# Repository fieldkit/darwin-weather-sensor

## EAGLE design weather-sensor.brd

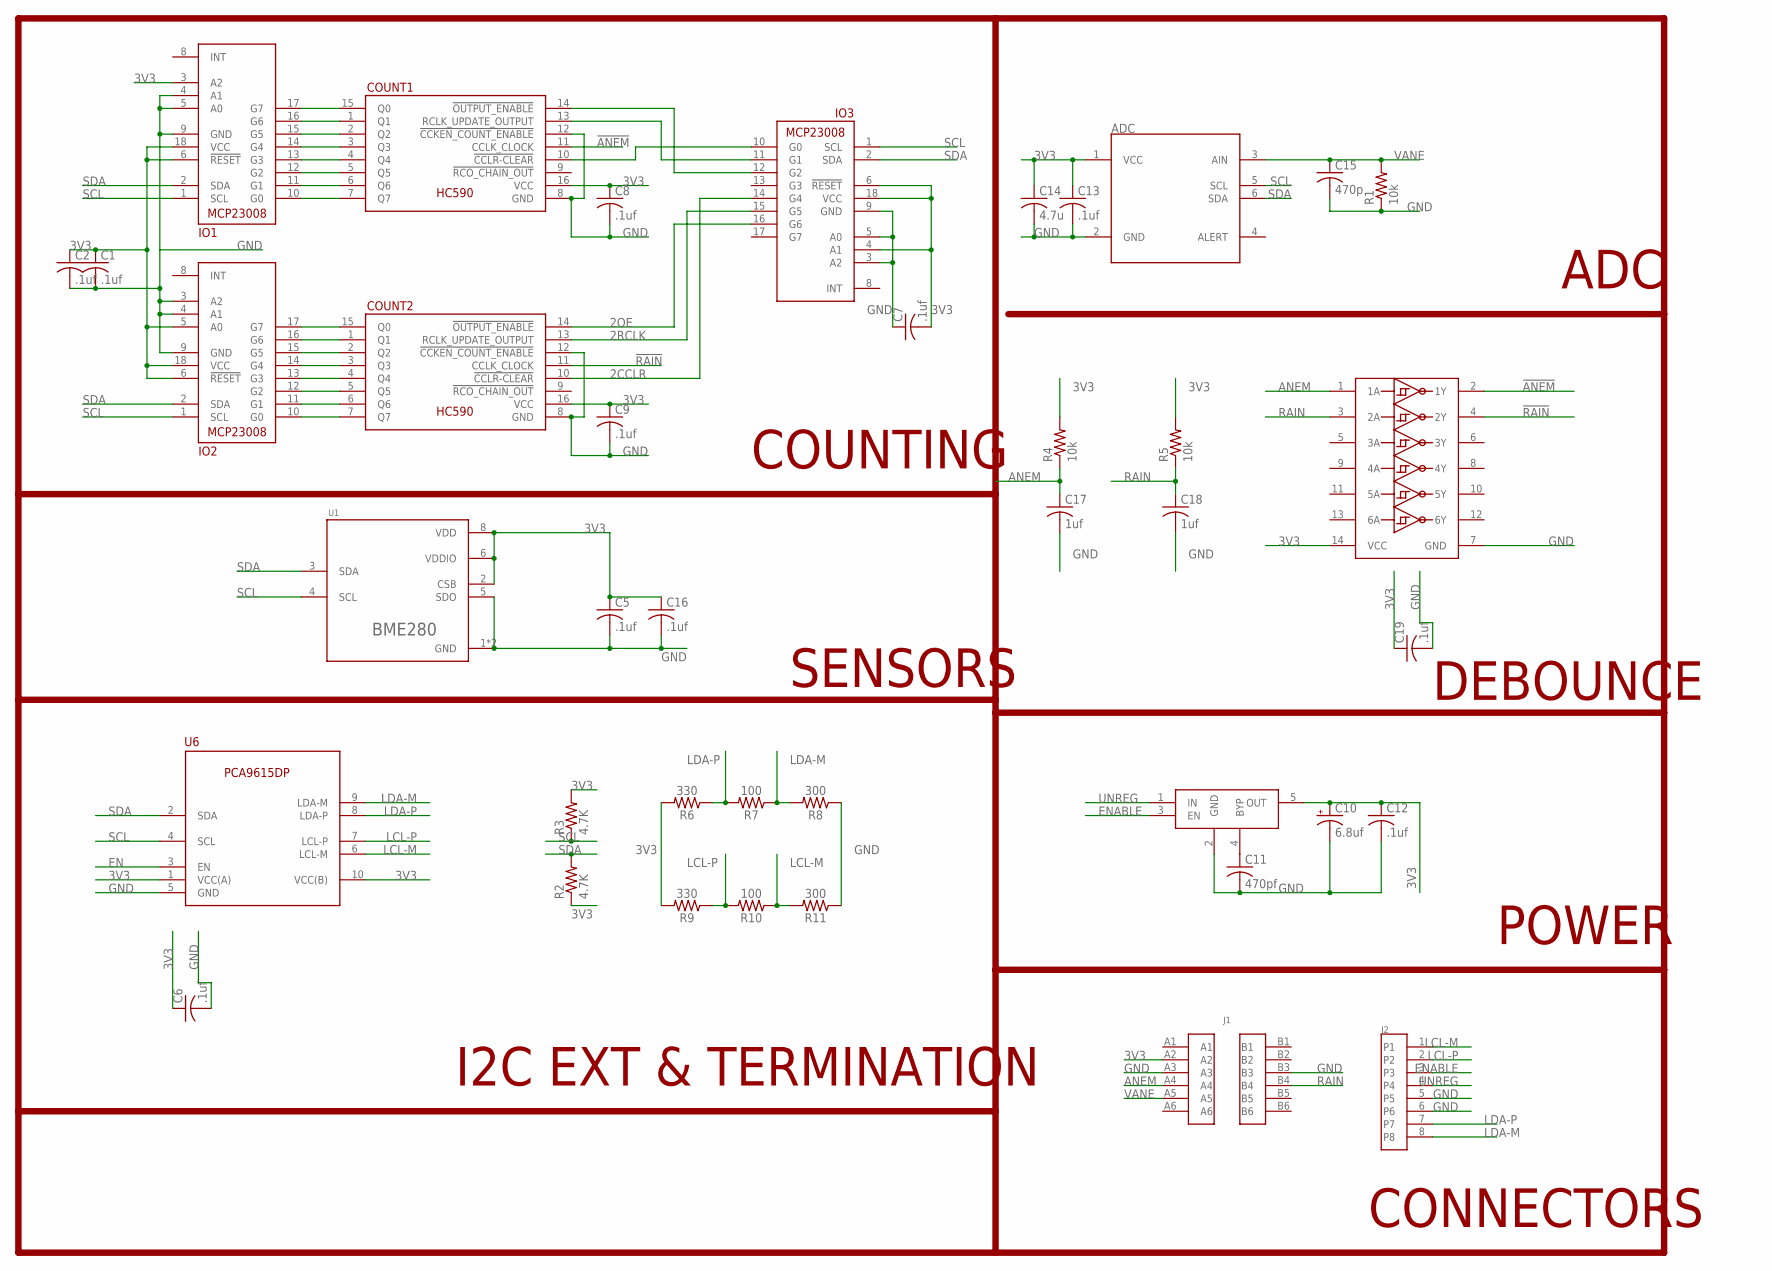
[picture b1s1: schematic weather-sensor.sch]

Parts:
ADC: ADC081C021SOT-DDC; SOP95P280X110-6
C1, C2, C5, C6, C7, C8, C9, C12, C13, C16, C19: .1uf; C0603K
C10: 6.8uf; A/3216-18R
C11: 470pf; C0603K
C14: 4.7u; C0603K
C15: 470p; C0603K
C17, C18: 1uf; C0603K
COUNT1, COUNT2: 74HC590; SOIC127P1050X265-16
INVERTER: 74HC14; SOIC127P780X200-14
IO1, IO2, IO3: MCP23008; SOIC18-W
J1: 43841-0005
J2: 95501-6889
R1, R4, R5: 10k; R0603
R2, R3: 4.7K; R0603
R6, R9: 330; 0603
R7, R10: 100; 0603
R8, R11: 300; 0603
U1: BME280; BM280
U5: MIC5219-3.3YM5-TR; SOT95P280X145-5
U6: PCA9615; SOP50P490X110-10

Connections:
2CCLR: COUNT2.10 (!CCLR-CLEAR), IO3.14 (G4)
2OE: COUNT2.14 (!OUTPUT_ENABLE), IO3.16 (G6)
2RCLK: COUNT2.13 (RCLK_UPDATE_OUTPUT), IO3.15 (G5)
3V3: ADC.1 (VCC), C1.1, C2.1, C5.1, C6.1, C7.2, C8.1, C9.1, C10.+, C12.1, C13.1, C14.1, C16.1, C19.1, COUNT1.16 (VCC), COUNT2.16 (VCC), INVERTER.14 (VCC), IO1.3 (A2), IO1.6 (!RESET), IO1.18 (VCC), IO2.5 (A0), IO2.6 (!RESET), IO2.18 (VCC), IO3.4 (A1), IO3.6 (!RESET), IO3.18 (VCC), J1.A2, R2.1, R3.2, R4.2, R5.2, R6.2, R9.2, U1.2 (CSB), U1.6 (VDDIO), U1.8 (VDD), U5.5 (OUT), U6.1 (VCC(A)), U6.10 (VCC(B))
!ANEM: COUNT1.11 (CCLK_CLOCK), INVERTER.2 (1Y)
!RAIN: COUNT2.11 (CCLK_CLOCK), INVERTER.4 (2Y)
ANEM: C17.1, INVERTER.1 (1A), J1.A4, R4.1
EN: U6.3 (EN)
ENABLE: J2.3, U5.3 (EN)
GND: ADC.2 (GND), C1.2, C2.2, C5.2, C6.2, C7.1, C8.2, C9.2, C10.-, C11.2, C12.2, C13.2, C14.2, C15.2, C16.2, C17.2, C18.2, C19.2, COUNT1.8 (GND), COUNT1.12 (!CCKEN_COUNT_ENABLE), COUNT2.8 (GND), COUNT2.12 (!CCKEN_COUNT_ENABLE), INVERTER.7 (GND), IO1.4 (A1), IO1.5 (A0), IO1.9 (GND), IO2.3 (A2), IO2.4 (A1), IO2.9 (GND), IO3.3 (A2), IO3.5 (A0), IO3.9 (GND), J1.A3, J1.B3, J2.5, J2.6, R1.1, R8.1, R11.1, U1.1 (GND), U1.5 (SDO), U1.7 (GND), U5.2 (GND), U6.5 (GND)
LCL-M: J2.1, R10.1, R11.2, U6.6 (LCL-M)
LCL-P: J2.2, R9.1, R10.2, U6.7 (LCL-P)
LDA-M: J2.8, R7.1, R8.2, U6.9 (LDA-M)
LDA-P: J2.7, R6.1, R7.2, U6.8 (LDA-P)
unnamed: COUNT2.15 (Q0), IO2.17 (G7)
unnamed: COUNT2.1 (Q1), IO2.16 (G6)
unnamed: COUNT2.2 (Q2), IO2.15 (G5)
unnamed: COUNT2.3 (Q3), IO2.14 (G4)
unnamed: COUNT2.4 (Q4), IO2.13 (G3)
unnamed: COUNT2.5 (Q5), IO2.12 (G2)
unnamed: COUNT2.6 (Q6), IO2.11 (G1)
unnamed: COUNT2.7 (Q7), IO2.10 (G0)
unnamed: COUNT1.15 (Q0), IO1.17 (G7)
unnamed: COUNT1.1 (Q1), IO1.16 (G6)
unnamed: COUNT1.2 (Q2), IO1.15 (G5)
unnamed: COUNT1.3 (Q3), IO1.14 (G4)
unnamed: COUNT1.4 (Q4), IO1.13 (G3)
unnamed: COUNT1.5 (Q5), IO1.12 (G2)
unnamed: COUNT1.6 (Q6), IO1.11 (G1)
unnamed: COUNT1.7 (Q7), IO1.10 (G0)
unnamed: COUNT1.14 (!OUTPUT_ENABLE), IO3.12 (G2)
unnamed: COUNT1.13 (RCLK_UPDATE_OUTPUT), IO3.11 (G1)
unnamed: COUNT1.10 (!CCLR-CLEAR), IO3.10 (G0)
unnamed: C11.1, U5.4 (BYP)
RAIN: C18.1, INVERTER.3 (2A), J1.B4, R5.1
SCL: ADC.5 (SCL), IO1.1 (SCL), IO2.1 (SCL), IO3.1 (SCL), R3.1, U1.4 (SCL), U6.4 (SCL)
SDA: ADC.6 (SDA), IO1.2 (SDA), IO2.2 (SDA), IO3.2 (SDA), R2.2, U1.3 (SDA), U6.2 (SDA)
UNREG: J2.4, U5.1 (IN)
VANE: ADC.3 (AIN), C15.1, J1.A5, R1.2

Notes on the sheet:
COUNTING
ADC
DEBOUNCE
POWER
CONNECTORS
I2C EXT & TERMINATION
SENSORS

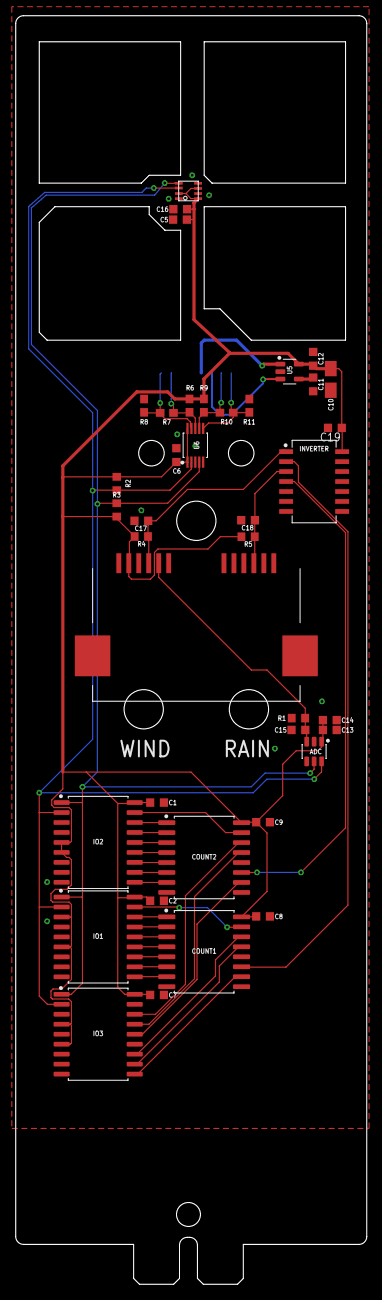
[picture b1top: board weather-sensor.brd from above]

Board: 2 copper layers, 44.7 x 161.5 mm, 40 parts (1 on the bottom side), 38 nets.

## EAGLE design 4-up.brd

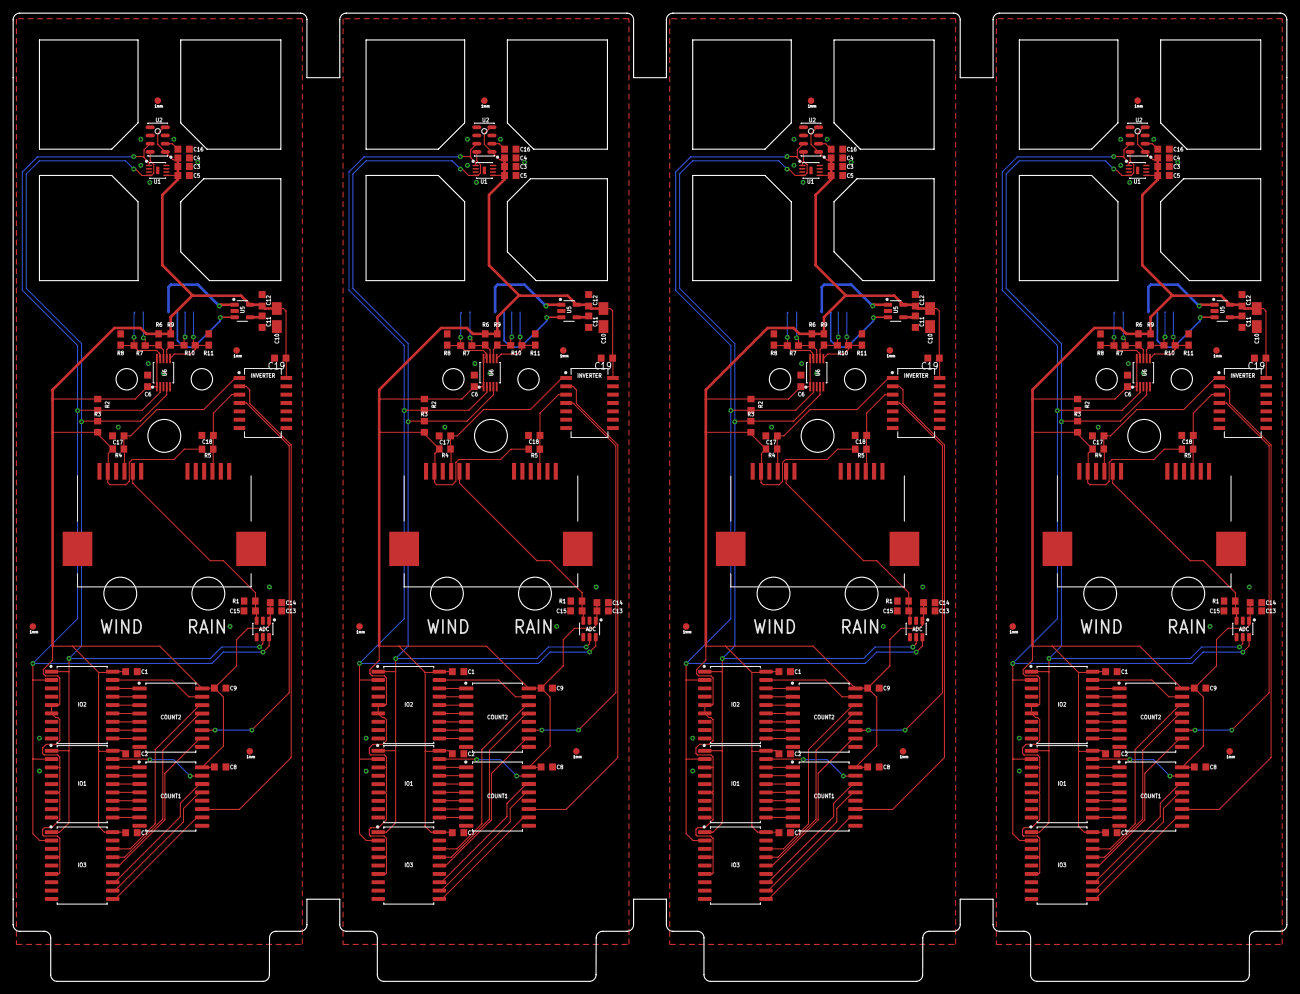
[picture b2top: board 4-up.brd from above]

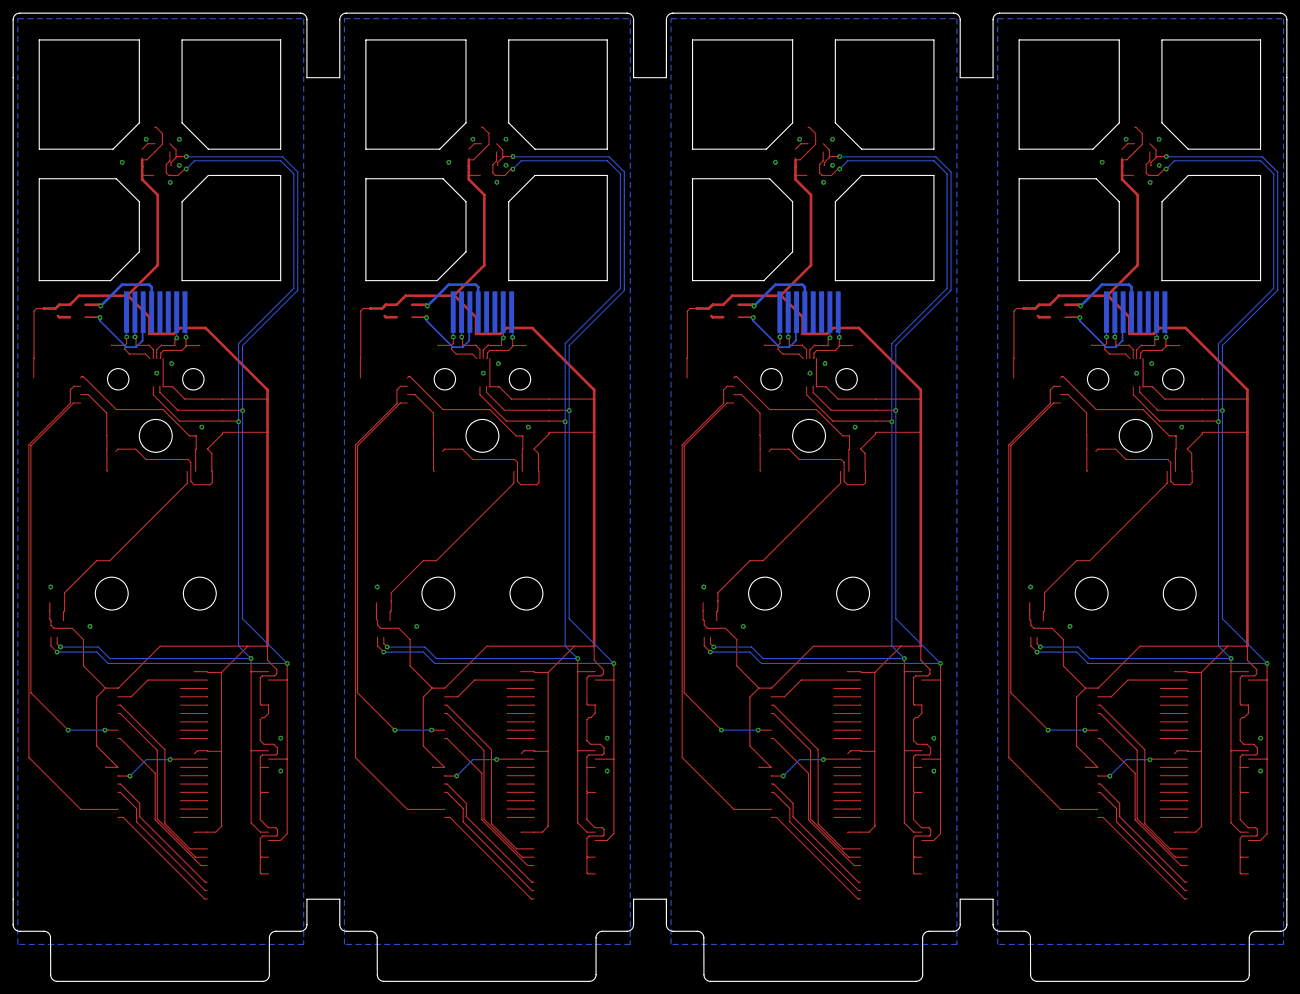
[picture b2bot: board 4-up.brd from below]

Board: 2 copper layers, 193.7 x 147.2 mm, 188 parts (4 on the bottom side), 78 nets.

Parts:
ADC, ADC1, ADC2, ADC3: ADC081C021SOT-DDC; SOP95P280X110-6
C1, C2, C3, C5, C6, C7, C8, C9, C12, C13, C16, C19, C20, C21, C22, C24, C25, C26, C27, C28, C31, C32, C35, C38, C39, C40, C41, C43, C44, C45, C46, C47, C50, C51, C54, C57, C58, C59, C60, C62, C63, C64, C65, C66, C69, C70, C73, C76: .1uf; C0603K
C4, C23, C42, C61: 10uf; C0603K
C10, C29, C48, C67: 6.8uf; A/3216-18R
C11, C30, C49, C68: 470pf; C0603K
C14, C33, C52, C71: 4.7u; C0603K
C15, C34, C53, C72: 470p; C0603K
C17, C18, C36, C37, C55, C56, C74, C75: 1uf; C0603K
COUNT1, COUNT2, COUNT3, COUNT4, COUNT5, COUNT6, COUNT7, COUNT8: 74HC590; SOIC127P1050X265-16
FID1, FID2, FID3, FID4, FID5, FID6, FID7, FID8, FID9, FID10, FID11, FID12, FID13, FID14, FID15, FID16: FIDUCIAL1X2.5; FIDUCIAL-1X2.5
INVERTER, INVERTER1, INVERTER2, INVERTER3: 74HC14; SOIC127P780X200-14
IO1, IO2, IO3, IO4, IO5, IO6, IO7, IO8, IO9, IO10, IO11, IO12: MCP23008; SOIC18-W
J1, J4, J6, J8: 43841-0005
J2, J3, J5, J7: 95501-6889
R1, R4, R5, R12, R15, R16, R23, R26, R27, R34, R37, R38: 10k; R0603
R2, R3, R13, R14, R24, R25, R35, R36: 4.7K; R0603
R6, R9, R17, R20, R28, R31, R39, R42: 330; 0603
R7, R10, R18, R21, R29, R32, R40, R43: 100; 0603
R8, R11, R19, R22, R30, R33, R41, R44: 300; 0603
U1, U3, U9, U13: SHT31; SON50P240X240X80-9T80
U2, U4, U10, U14: MPL3115A2LGA8; SON125P300X500X110-8
U5, U7, U11, U15: MIC5219-3.3YM5-TR; SOT95P280X145-5
U6, U8, U12, U16: PCA9615; SOP50P490X110-10

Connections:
2CCLR: COUNT2.10, IO3.14
2CCLR1: COUNT4.10, IO6.14
2OE: COUNT2.14, IO3.16
2OE1: COUNT4.14, IO6.16
2RCLK: COUNT2.13, IO3.15
2RCLK1: COUNT4.13, IO6.15
3V1: ADC1.1, C20.1, C21.1, C22.1, C23.1, C24.1, C25.1, C26.2, C27.1, C28.1, C29.+, C31.1, C32.1, C33.1, C38.1, COUNT3.16, COUNT4.16, INVERTER1.14, IO4.5, IO4.6, IO4.18, IO5.3, IO5.6, IO5.18, IO6.4, IO6.6, IO6.18, J4.A2, R13.1, R14.2, R15.2, R16.2, R17.2, R20.2, U3.5, U4.1, U4.4, U7.5, U8.1, U8.10
3V3: ADC.1, C1.1, C2.1, C3.1, C4.1, C5.1, C6.1, C7.2, C8.1, C9.1, C10.+, C12.1, C13.1, C14.1, C19.1, COUNT1.16, COUNT2.16, INVERTER.14, IO1.3, IO1.6, IO1.18, IO2.5, IO2.6, IO2.18, IO3.4, IO3.6, IO3.18, J1.A2, R2.1, R3.2, R4.2, R5.2, R6.2, R9.2, U1.5, U2.1, U2.4, U5.5, U6.1, U6.10
!ANEM: COUNT1.11, INVERTER.2
!ANEM1: COUNT3.11, INVERTER1.2
!RAIN: COUNT2.11, INVERTER.4
!RAIN1: COUNT4.11, INVERTER1.4
ANEM: C17.1, INVERTER.1, J1.A4, R4.1
ANEM1: C36.1, INVERTER1.1, J4.A4, R15.1
CAP: C16.1, U2.2
CAP1: C35.1, U4.2
ENABLE: J2.3, U5.3
ENABLE1: J3.3, U7.3
GND: ADC.2, C1.2, C2.2, C3.2, C4.2, C5.2, C6.2, C7.1, C8.2, C9.2, C10.-, C11.2, C12.2, C13.2, C14.2, C15.2, C16.2, C17.2, C18.2, C19.2, COUNT1.8, COUNT1.12, COUNT2.8, COUNT2.12, INVERTER.7, IO1.4, IO1.5, IO1.9, IO2.3, IO2.4, IO2.9, IO3.3, IO3.5, IO3.9, J1.A3, J1.B3, J2.5, J2.6, R1.1, R8.1, R11.1, U1.2, U1.7, U1.8, U2.3, U5.2, U6.5
GND1: ADC1.2, C20.2, C21.2, C22.2, C23.2, C24.2, C25.2, C26.1, C27.2, C28.2, C29.-, C30.2, C31.2, C32.2, C33.2, C34.2, C35.2, C36.2, C37.2, C38.2, COUNT3.8, COUNT3.12, COUNT4.8, COUNT4.12, INVERTER1.7, IO4.3, IO4.4, IO4.9, IO5.4, IO5.5, IO5.9, IO6.3, IO6.5, IO6.9, J3.5, J3.6, J4.A3, J4.B3, R12.1, R19.1, R22.1, U3.2, U3.7, U3.8, U4.3, U7.2, U8.5
LCL-M: J2.1, R10.1, R11.2, U6.6
LCL-M1: J3.1, R21.1, R22.2, U8.6
LCL-P: J2.2, R9.1, R10.2, U6.7
LCL-P1: J3.2, R20.1, R21.2, U8.7
LDA-M: J2.8, R7.1, R8.2, U6.9
LDA-M1: J3.8, R18.1, R19.2, U8.9
LDA-P: J2.7, R6.1, R7.2, U6.8
LDA-P1: J3.7, R17.1, R18.2, U8.8
unnamed: COUNT2.15, IO2.17
unnamed: COUNT2.1, IO2.16
unnamed: COUNT2.2, IO2.15
unnamed: COUNT2.3, IO2.14
unnamed: COUNT2.4, IO2.13
unnamed: COUNT2.5, IO2.12
unnamed: COUNT2.6, IO2.11
unnamed: COUNT2.7, IO2.10
unnamed: COUNT1.15, IO1.17
unnamed: COUNT1.1, IO1.16
unnamed: COUNT4.15, IO4.17
unnamed: COUNT1.2, IO1.15
unnamed: COUNT1.3, IO1.14
unnamed: COUNT1.4, IO1.13
unnamed: COUNT1.5, IO1.12
unnamed: COUNT1.6, IO1.11
unnamed: COUNT1.7, IO1.10
unnamed: COUNT1.14, IO3.12
unnamed: COUNT1.13, IO3.11
unnamed: COUNT1.10, IO3.10
unnamed: COUNT4.1, IO4.16
unnamed: COUNT4.2, IO4.15
unnamed: C11.1, U5.4
unnamed: COUNT4.3, IO4.14
unnamed: COUNT4.4, IO4.13
unnamed: COUNT4.5, IO4.12
unnamed: COUNT4.6, IO4.11
unnamed: COUNT4.7, IO4.10
unnamed: COUNT3.15, IO5.17
unnamed: COUNT3.1, IO5.16
unnamed: COUNT3.2, IO5.15
unnamed: COUNT3.3, IO5.14
unnamed: COUNT3.4, IO5.13
unnamed: COUNT3.5, IO5.12
unnamed: COUNT3.6, IO5.11
unnamed: COUNT3.7, IO5.10
unnamed: COUNT3.14, IO6.12
unnamed: COUNT3.13, IO6.11
unnamed: COUNT3.10, IO6.10
unnamed: C30.1, U7.4
RAIN: C18.1, INVERTER.3, J1.B4, R5.1
RAIN1: C37.1, INVERTER1.3, J4.B4, R16.1
SCL: ADC.5, IO1.1, IO2.1, IO3.1, R3.1, U1.4, U2.8, U6.4
SCL1: ADC1.5, IO4.1, IO5.1, IO6.1, R14.1, U3.4, U4.8, U8.4
SDA: ADC.6, IO1.2, IO2.2, IO3.2, R2.2, U1.1, U2.7, U6.2
SDA1: ADC1.6, IO4.2, IO5.2, IO6.2, R13.2, U3.1, U4.7, U8.2
UNREG: J2.4, U5.1
UNREG1: J3.4, U7.1
VANE: ADC.3, C15.1, J1.A5, R1.2
VANE1: ADC1.3, C34.1, J4.A5, R12.2

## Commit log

2019-07-17 Test Article 1
2019-09-04 Changed range extender and added debounce to switched inputs.
2019-10-17 Changed power architecture for module/sesnor power synchronization. TA4.
2020-02-11 New Panel
2020-08-06 Replaced sensors with BME280, Reworked outline for compatibility with new arm.
2020-10-23 Cleaned up deprecated files.

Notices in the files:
parts and their libraries:
SparkFun-Resistors: Licensing: Creative Commons ShareAlike 4.0 International - https://creativecommons.org/licenses/by-sa/4.0
